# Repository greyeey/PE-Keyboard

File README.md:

# PE-Keyboard
 PE Sideproject to create a usefull macro type keyboard

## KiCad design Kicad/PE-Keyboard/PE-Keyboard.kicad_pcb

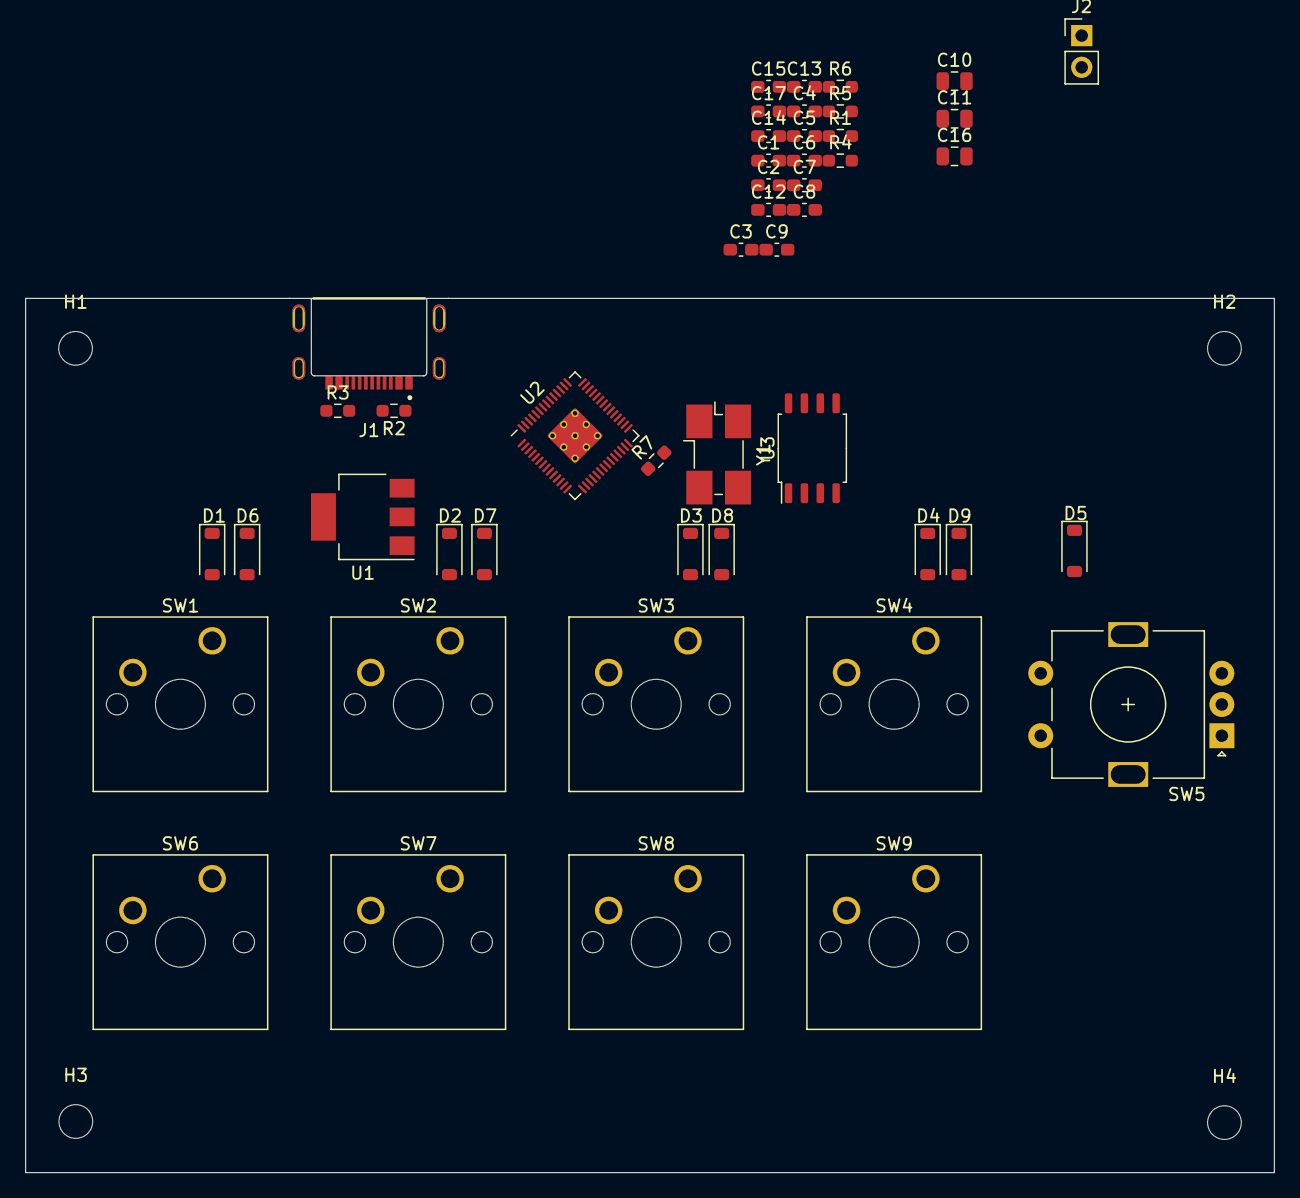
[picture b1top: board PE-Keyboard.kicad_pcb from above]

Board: 2 copper layers, 100.0 x 70.0 mm, 52 parts (0 on the bottom side), 35 nets, no tracks yet.

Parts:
C1, C2, C3, C4, C5, C6, C7, C8, C9, C14: 100n; C_0603_1608Metric_Pad1.08x0.95mm_HandSolder
C10, C11, C16: 10u; C_0805_2012Metric
C12, C13: 1u; C_0603_1608Metric_Pad1.08x0.95mm_HandSolder
C15, C17: 13p; C_0603_1608Metric_Pad1.08x0.95mm_HandSolder
D1, D2, D3, D4, D5, D6, D7, D8, D9: 1N4148; D_SOD-123
H1, H2, H3, H4: MountingHole; MountingHole_2.7mm_M2.5
J1: USB4510-03-1-A_REVA; GCT_USB4510-03-1-A_REVA
J2: Conn_01x02; PinHeader_1x02_P2.54mm_Vertical
R1, R4: 27; R_0603_1608Metric_Pad0.98x0.95mm_HandSolder
R2, R3: 5.1K; R_0603_1608Metric_Pad0.98x0.95mm_HandSolder
R5: DNF; R_0603_1608Metric_Pad0.98x0.95mm_HandSolder
R6, R7: 1k; R_0603_1608Metric_Pad0.98x0.95mm_HandSolder
SW1, SW2, SW3, SW4, SW6, SW7, SW8, SW9: SW_Push; SW_Cherry_MX_1.00u_PCB
SW5: RotaryEncoder_Switch; RotaryEncoder_Alps_EC11E-Switch_Vertical_H20mm
U1: NCP1117-3.3_SOT223; SOT-223-3_TabPin2
U2: RP2040; RP2040-QFN-56
U3: W25Q128JVS; SOIC-8_5.23x5.23mm_P1.27mm
Y1: Crystal_GND24; Crystal_SMD_0603-4Pin_6.0x3.5mm_HandSoldering

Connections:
+1V1: C1.1, C2.1, C12.1, U2.23 (DVDD), U2.45 (VREG_VOUT), U2.50 (DVDD)
+3V3: C3.1, C4.1, C5.1, C6.1, C7.1, C8.1, C9.1, C11.1, C13.1, C14.1, C16.1, R5.1, U1.2 (VO), U2.1 (IOVDD), U2.10 (IOVDD), U2.22 (IOVDD), U2.33 (IOVDD), U2.42 (IOVDD), U2.43 (ADC_AVDD), U2.44 (VREG_IN), U2.48 (USB_VDD), U2.49 (IOVDD), U3.8 (VCC)
/KeyboardMatrix/Col0: D1.1 (K), D6.1 (K)
/KeyboardMatrix/Col1: D2.1 (K), D7.1 (K)
/KeyboardMatrix/Col2: D3.1 (K), D8.1 (K)
/KeyboardMatrix/Col3: D4.1 (K), D9.1 (K)
/KeyboardMatrix/Row0: SW1.2, SW2.2, SW3.2, SW4.2, SW5.S1
/KeyboardMatrix/Row1: SW6.2, SW7.2, SW8.2, SW9.2
/Microcontroller/QSPI_SCLK: U2.52 (QSPI_SCLK), U3.6 (CLK)
/Microcontroller/QSPI_SD0: U2.53 (QSPI_SD0), U3.5 (DI(IO0))
/Microcontroller/QSPI_SD1: U2.55 (QSPI_SD1), U3.2 (DO(IO1))
/Microcontroller/QSPI_SD2: U2.54 (QSPI_SD2), U3.3 (IO2)
/Microcontroller/QSPI_SD3: U2.51 (QSPI_SD3), U3.7 (IO3)
/Microcontroller/QSPI_SS: R5.2, R6.1, U2.56 (QSPI_SS), U3.1 (~CS)
/Microcontroller/USB_D+: J1.A6 (DP1), J1.B6 (DP2), R1.1
/Microcontroller/USB_D-: J1.A7 (DN1), J1.B7 (DN2), R4.1
/Microcontroller/XIN: C15.1, U2.20 (XIN), Y1.3
/Microcontroller/XOUT: R7.1, U2.21 (XOUT)
/Microcontroller/~USB_BOOT: J2.1, R6.2
GND: C1.2, C2.2, C3.2, C4.2, C5.2, C6.2, C7.2, C8.2, C9.2, C10.2, C11.2, C12.2, C13.2, C14.2, C15.2, C16.2, C17.2, J1.A1_B12 (GND_A), J1.B1_A12 (GND_B), J1.S1 (SHELL_GND), J1.S2 (SHELL_GND__1), J1.S3 (SHELL_GND__2), J1.S4 (SHELL_GND__3), J2.2, R2.1, R3.1, SW5.C, U1.1 (GND), U2.19 (TESTEN), U2.57 (GND), U3.4 (GND), Y1.2, Y1.4
unnamed: C17.1, R7.2, Y1.1
unnamed: D1.2 (A), SW1.1
unnamed: D2.2 (A), SW2.1
unnamed: D3.2 (A), SW3.1
unnamed: D4.2 (A), SW4.1
unnamed: D5.2 (A), SW5.S2
unnamed: D6.2 (A), SW6.1
unnamed: D7.2 (A), SW7.1
unnamed: D8.2 (A), SW8.1
unnamed: D9.2 (A), SW9.1
unnamed: J1.A5 (CC1), R2.2
unnamed: J1.B5 (CC2), R3.2
unnamed: R4.2, U2.46 (USB_DM)
unnamed: R1.2, U2.47 (USB_DP)
VBUS: C10.1, J1.A4_B9 (VBUS_A), J1.B4_A9 (VBUS_B), U1.3 (VI)

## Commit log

2023-12-22 Main PCB Schematic structure
    from which we can branch off.
2023-12-22 Added components
2023-12-22 Gitignore hit?
2024-02-05 Update Gitignore
    Maybe it will finally ignore file "locks"
2024-02-05 Started Sch and PCB
    Laid out the buttons/Encoder. Chose a nice crystal, realized a connector in board gives challenges with routing.
